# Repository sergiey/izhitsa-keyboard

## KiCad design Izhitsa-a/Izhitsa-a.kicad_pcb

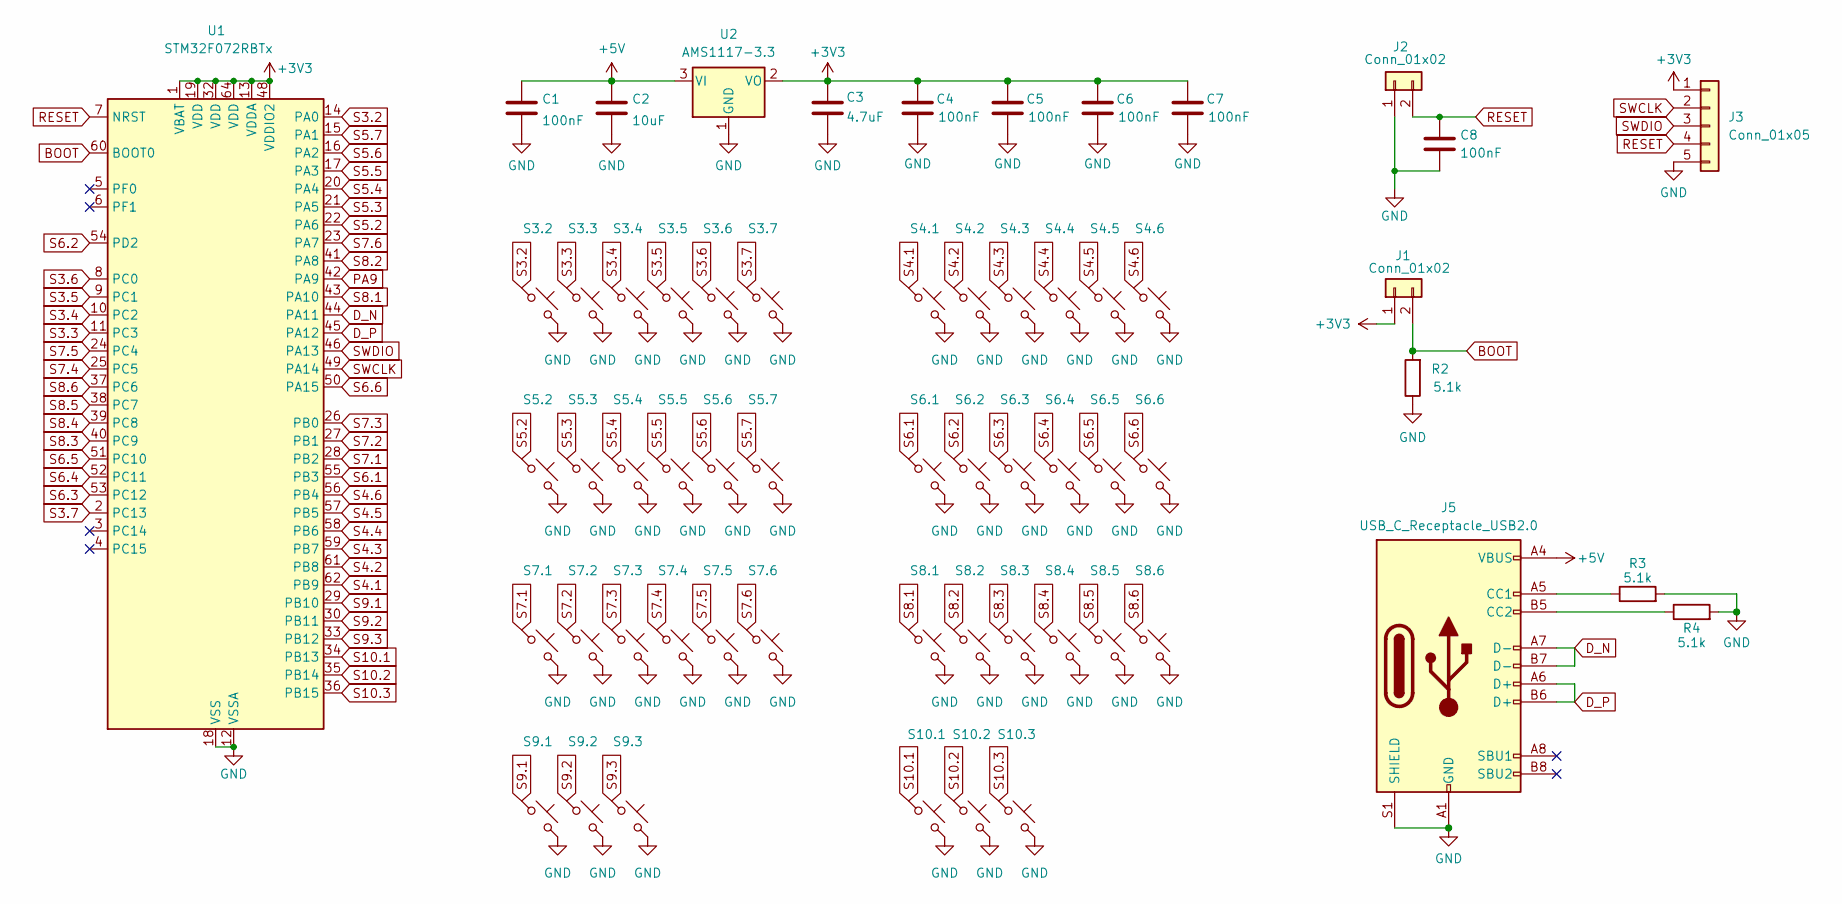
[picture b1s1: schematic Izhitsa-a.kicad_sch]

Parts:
C1, C4, C5, C6, C7, C8: 100nF; C_0603_1608Metric
C2: 10uF; C_0603_1608Metric
C3: 4.7uF; C_0603_1608Metric
J1, J2: Conn_01x02; PinHeader_1x02_P2.54mm_Vertical
J3: Conn_01x05; PinHeader_1x05_P2.54mm_Vertical
J5: USB_C_Receptacle_USB2.0; USB_C_Receptacle_HRO_TYPE-C-31-M-12
R2, R3, R4: 5.1k; R_0603_1608Metric
S3.2, S3.3, S3.4, S3.5, S3.6, S3.7, S4.1, S4.2, S4.3, S4.4, S4.5, S4.6, S5.2, S5.3, S5.4, S5.5, S5.6, S5.7, S6.1, S6.2, S6.3, S6.4, S6.5, S6.6, S7.1, S7.2, S7.3, S7.4, S7.5, S7.6, S8.1, S8.2, S8.3, S8.4, S8.5, S8.6, S9.1, S9.2, S9.3, S10.1, S10.2, S10.3: Keyswitch; Choc_V1_1.00u
U1: STM32F072RBTx; LQFP-64_10x10mm_P0.5mm
U2: AMS1117-3.3; SOT-223-3_TabPin2

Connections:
+3V3: C3.1, C4.1, C5.1, C6.1, C7.1, J1.1, J3.1, U1.1 (VBAT), U1.13 (VDDA), U1.19 (VDD), U1.32 (VDD), U1.48 (VDDIO2), U1.64 (VDD), U2.2 (VO)
+5V: C1.1, C2.1, J5.A4 (VBUS), J5.A9 (VBUS), J5.B4 (VBUS), J5.B9 (VBUS), U2.3 (VI)
BOOT: J1.2, R2.2, U1.60 (BOOT0)
D_N: J5.A7 (D-), J5.B7 (D-), U1.44 (PA11)
D_P: J5.A6 (D+), J5.B6 (D+), U1.45 (PA12)
GND: C1.2, C2.2, C3.2, C4.2, C5.2, C6.2, C7.2, C8.2, J2.1, J3.5, J5.A1 (GND), J5.A12 (GND), J5.B1 (GND), J5.B12 (GND), J5.S1 (SHIELD), R2.1, R3.2, R4.2, S3.2.2, S3.3.2, S3.4.2, S3.5.2, S3.6.2, S3.7.2, S4.1.2, S4.2.2, S4.3.2, S4.4.2, S4.5.2, S4.6.2, S5.2.2, S5.3.2, S5.4.2, S5.5.2, S5.6.2, S5.7.2, S6.1.2, S6.2.2, S6.3.2, S6.4.2, S6.5.2, S6.6.2, S7.1.2, S7.2.2, S7.3.2, S7.4.2, S7.5.2, S7.6.2, S8.1.2, S8.2.2, S8.3.2, S8.4.2, S8.5.2, S8.6.2, S9.1.2, S9.2.2, S9.3.2, S10.1.2, S10.2.2, S10.3.2, U1.12 (VSSA), U1.18 (VSS), U1.31 (VSS), U1.47 (VSS), U1.63 (VSS), U2.1 (GND)
unnamed: J5.A5 (CC1), R3.1
unnamed: J5.B5 (CC2), R4.1
PA9: U1.42 (PA9)
RESET: C8.1, J2.2, J3.4, U1.7 (NRST)
S3.2: S3.2.1, U1.14 (PA0)
S3.3: S3.3.1, U1.11 (PC3)
S3.4: S3.4.1, U1.10 (PC2)
S3.5: S3.5.1, U1.9 (PC1)
S3.6: S3.6.1, U1.8 (PC0)
S3.7: S3.7.1, U1.2 (PC13)
S4.1: S4.1.1, U1.62 (PB9)
S4.2: S4.2.1, U1.61 (PB8)
S4.3: S4.3.1, U1.59 (PB7)
S4.4: S4.4.1, U1.58 (PB6)
S4.5: S4.5.1, U1.57 (PB5)
S4.6: S4.6.1, U1.56 (PB4)
S5.2: S5.2.1, U1.22 (PA6)
S5.3: S5.3.1, U1.21 (PA5)
S5.4: S5.4.1, U1.20 (PA4)
S5.5: S5.5.1, U1.17 (PA3)
S5.6: S5.6.1, U1.16 (PA2)
S5.7: S5.7.1, U1.15 (PA1)
S6.1: S6.1.1, U1.55 (PB3)
S6.2: S6.2.1, U1.54 (PD2)
S6.3: S6.3.1, U1.53 (PC12)
S6.4: S6.4.1, U1.52 (PC11)
S6.5: S6.5.1, U1.51 (PC10)
S6.6: S6.6.1, U1.50 (PA15)
S7.1: S7.1.1, U1.28 (PB2)
S7.2: S7.2.1, U1.27 (PB1)
S7.3: S7.3.1, U1.26 (PB0)
S7.4: S7.4.1, U1.25 (PC5)
S7.5: S7.5.1, U1.24 (PC4)
S7.6: S7.6.1, U1.23 (PA7)
S8.1: S8.1.1, U1.43 (PA10)
S8.2: S8.2.1, U1.41 (PA8)
S8.3: S8.3.1, U1.40 (PC9)
S8.4: S8.4.1, U1.39 (PC8)
S8.5: S8.5.1, U1.38 (PC7)
S8.6: S8.6.1, U1.37 (PC6)
S9.1: S9.1.1, U1.29 (PB10)
S9.2: S9.2.1, U1.30 (PB11)
S9.3: S9.3.1, U1.33 (PB12)
S10.1: S10.1.1, U1.34 (PB13)
S10.2: S10.2.1, U1.35 (PB14)
S10.3: S10.3.1, U1.36 (PB15)
SWCLK: J3.2, U1.49 (PA14)
SWDIO: J3.3, U1.46 (PA13)

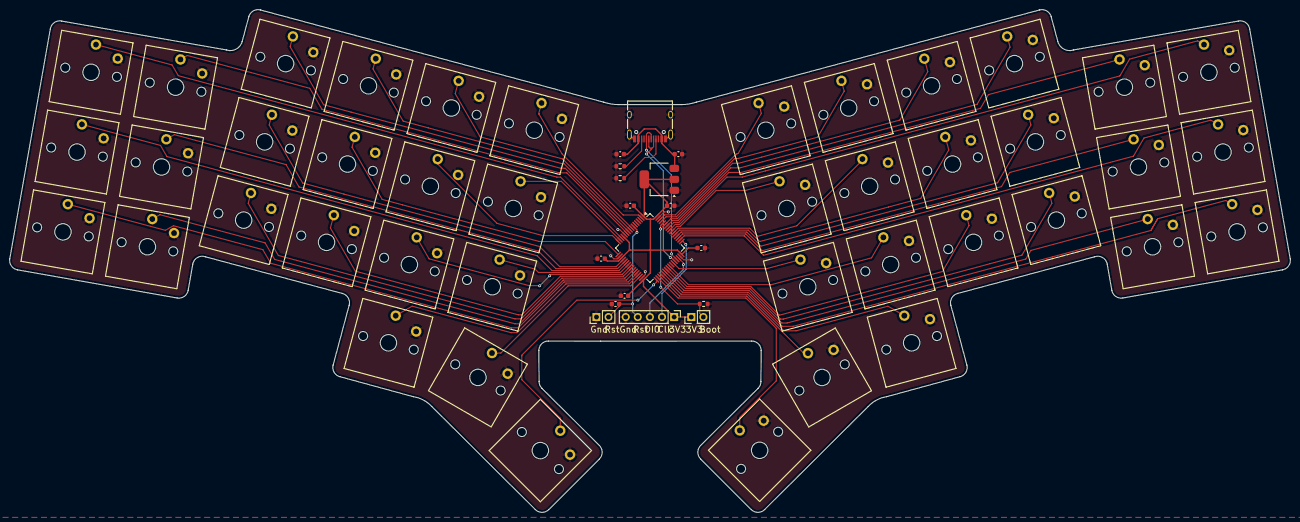
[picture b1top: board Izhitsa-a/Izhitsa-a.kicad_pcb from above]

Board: 2 copper layers, 268.7 x 105.5 mm, 59 parts (0 on the bottom side), 53 nets.

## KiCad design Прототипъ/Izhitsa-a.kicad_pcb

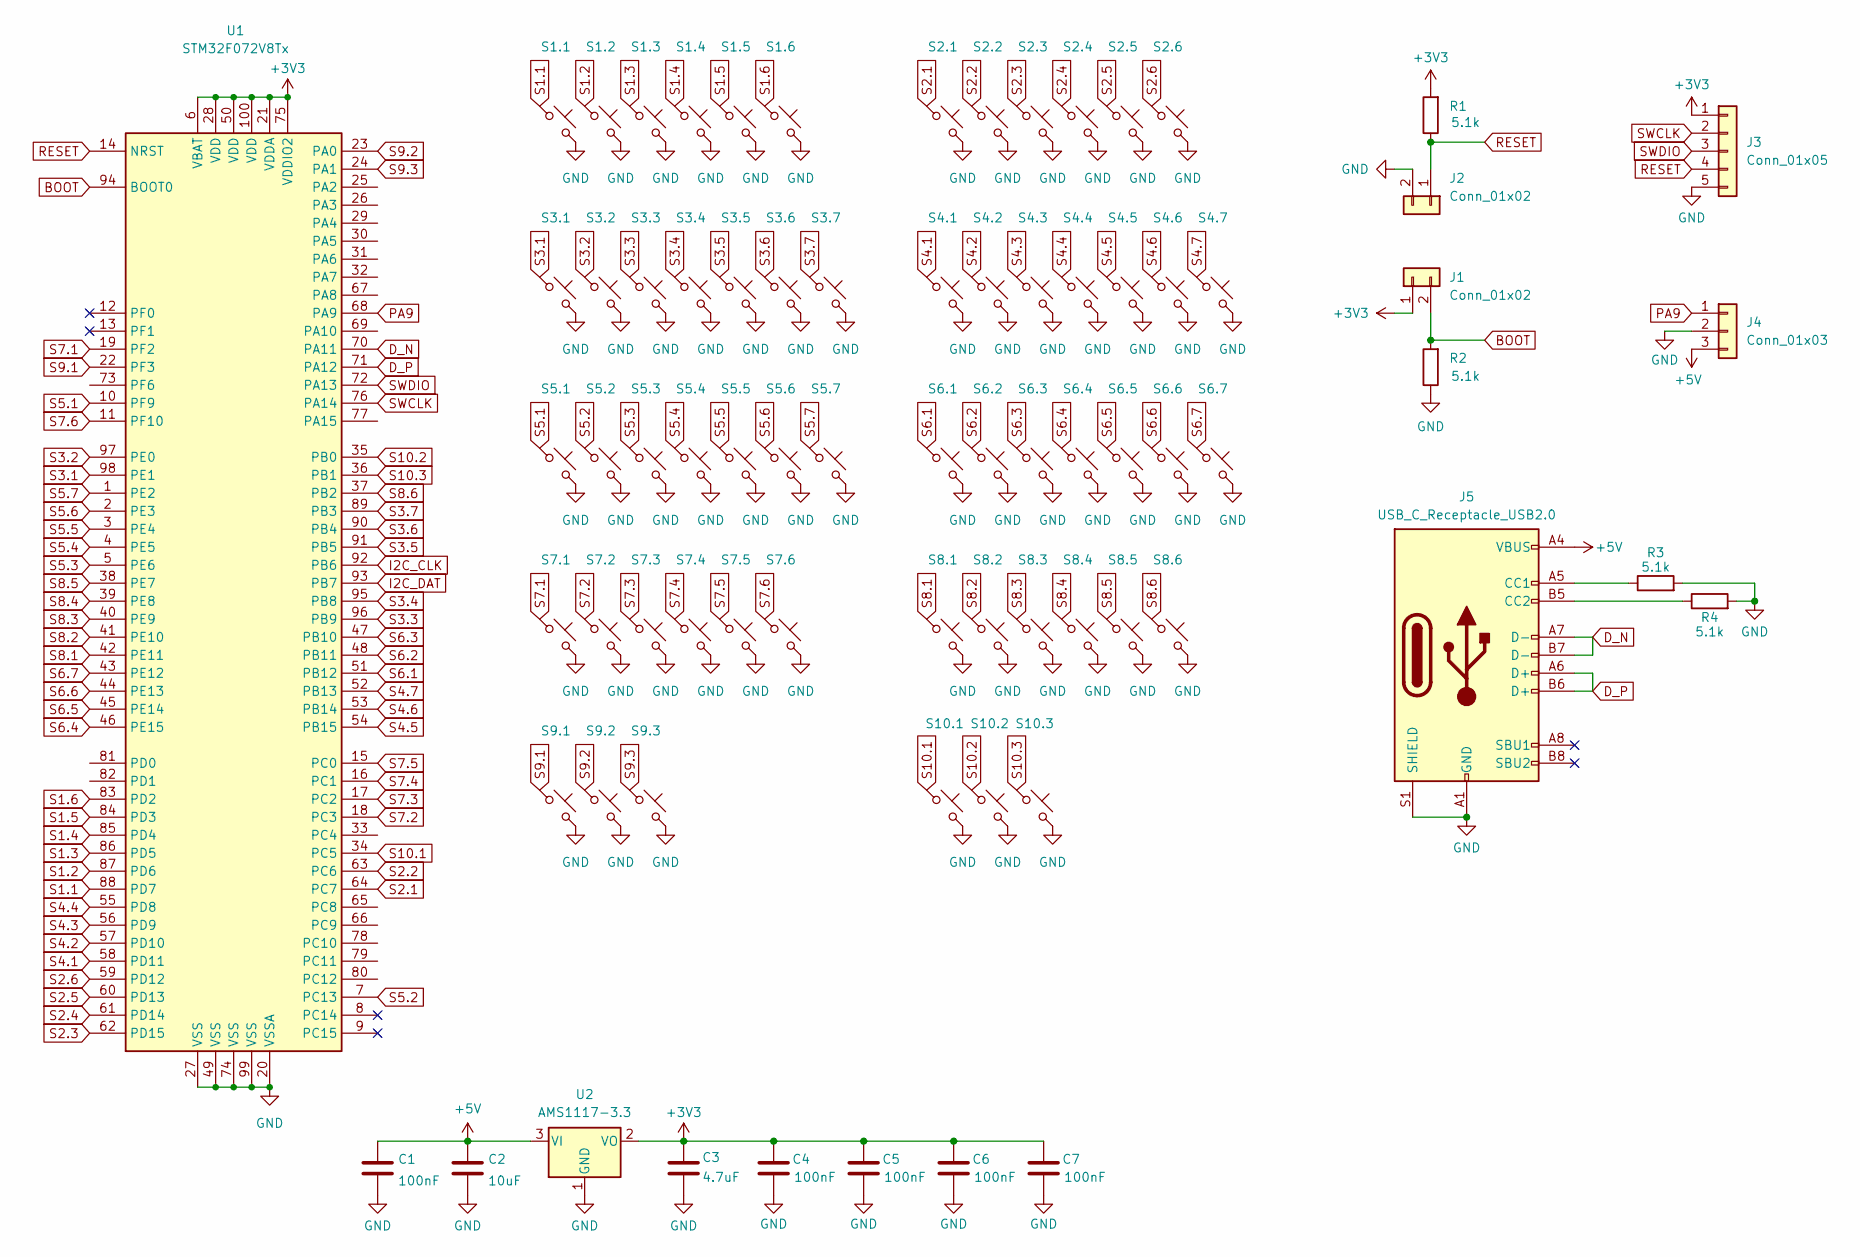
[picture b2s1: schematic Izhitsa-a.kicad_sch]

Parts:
C1, C4, C5, C6, C7: 100nF; C_0603_1608Metric
C2: 10uF; C_0603_1608Metric
C3: 4.7uF; C_0603_1608Metric
J1, J2: Conn_01x02; PinHeader_1x02_P2.54mm_Vertical
J3: Conn_01x05; PinHeader_1x05_P2.54mm_Vertical
J4: Conn_01x03; PinHeader_1x03_P2.54mm_Vertical
J5: USB_C_Receptacle_USB2.0; USB_C_Receptacle_HRO_TYPE-C-31-M-12
R1, R2, R3, R4: 5.1k; R_0603_1608Metric
S1.1, S1.2, S1.3, S1.4, S1.5, S1.6, S2.1, S2.2, S2.3, S2.4, S2.5, S2.6, S3.1, S3.2, S3.3, S3.4, S3.5, S3.6, S3.7, S4.1, S4.2, S4.3, S4.4, S4.5, S4.6, S4.7, S5.1, S5.2, S5.3, S5.4, S5.5, S5.6, S5.7, S6.1, S6.2, S6.3, S6.4, S6.5, S6.6, S6.7, S7.1, S7.2, S7.3, S7.4, S7.5, S7.6, S8.1, S8.2, S8.3, S8.4, S8.5, S8.6, S9.1, S9.2, S9.3, S10.1, S10.2, S10.3: Keyswitch; Choc_V1_1.00u
U1: STM32F072V8Tx; LQFP-100_14x14mm_P0.5mm
U2: AMS1117-3.3; SOT-223-3_TabPin2

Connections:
+3V3: C3.1, C4.1, C5.1, C6.1, C7.1, J1.1, J3.1, R1.2, U1.6 (VBAT), U1.21 (VDDA), U1.28 (VDD), U1.50 (VDD), U1.75 (VDDIO2), U1.100 (VDD), U2.2 (VO)
+5V: C1.1, C2.1, J4.3, J5.A4 (VBUS), J5.A9 (VBUS), J5.B4 (VBUS), J5.B9 (VBUS), U2.3 (VI)
BOOT: J1.2, R2.2, U1.94 (BOOT0)
D_N: J5.A7 (D-), J5.B7 (D-), U1.70 (PA11)
D_P: J5.A6 (D+), J5.B6 (D+), U1.71 (PA12)
GND: C1.2, C2.2, C3.2, C4.2, C5.2, C6.2, C7.2, J2.2, J3.5, J4.2, J5.A1 (GND), J5.A12 (GND), J5.B1 (GND), J5.B12 (GND), J5.S1 (SHIELD), R2.1, R3.2, R4.2, S1.1.2, S1.2.2, S1.3.2, S1.4.2, S1.5.2, S1.6.2, S2.1.2, S2.2.2, S2.3.2, S2.4.2, S2.5.2, S2.6.2, S3.1.2, S3.2.2, S3.3.2, S3.4.2, S3.5.2, S3.6.2, S3.7.2, S4.1.2, S4.2.2, S4.3.2, S4.4.2, S4.5.2, S4.6.2, S4.7.2, S5.1.2, S5.2.2, S5.3.2, S5.4.2, S5.5.2, S5.6.2, S5.7.2, S6.1.2, S6.2.2, S6.3.2, S6.4.2, S6.5.2, S6.6.2, S6.7.2, S7.1.2, S7.2.2, S7.3.2, S7.4.2, S7.5.2, S7.6.2, S8.1.2, S8.2.2, S8.3.2, S8.4.2, S8.5.2, S8.6.2, S9.1.2, S9.2.2, S9.3.2, S10.1.2, S10.2.2, S10.3.2, U1.20 (VSSA), U1.27 (VSS), U1.49 (VSS), U1.74 (VSS), U1.99 (VSS), U2.1 (GND)
I2C_CLK: U1.92 (PB6)
I2C_DAT: U1.93 (PB7)
unnamed: J5.A5 (CC1), R3.1
unnamed: J5.B5 (CC2), R4.1
PA9: J4.1, U1.68 (PA9)
RESET: J2.1, J3.4, R1.1, U1.14 (NRST)
S1.1: S1.1.1, U1.88 (PD7)
S1.2: S1.2.1, U1.87 (PD6)
S1.3: S1.3.1, U1.86 (PD5)
S1.4: S1.4.1, U1.85 (PD4)
S1.5: S1.5.1, U1.84 (PD3)
S1.6: S1.6.1, U1.83 (PD2)
S2.1: S2.1.1, U1.64 (PC7)
S2.2: S2.2.1, U1.63 (PC6)
S2.3: S2.3.1, U1.62 (PD15)
S2.4: S2.4.1, U1.61 (PD14)
S2.5: S2.5.1, U1.60 (PD13)
S2.6: S2.6.1, U1.59 (PD12)
S3.1: S3.1.1, U1.98 (PE1)
S3.2: S3.2.1, U1.97 (PE0)
S3.3: S3.3.1, U1.96 (PB9)
S3.4: S3.4.1, U1.95 (PB8)
S3.5: S3.5.1, U1.91 (PB5)
S3.6: S3.6.1, U1.90 (PB4)
S3.7: S3.7.1, U1.89 (PB3)
S4.1: S4.1.1, U1.58 (PD11)
S4.2: S4.2.1, U1.57 (PD10)
S4.3: S4.3.1, U1.56 (PD9)
S4.4: S4.4.1, U1.55 (PD8)
S4.5: S4.5.1, U1.54 (PB15)
S4.6: S4.6.1, U1.53 (PB14)
S4.7: S4.7.1, U1.52 (PB13)
S5.1: S5.1.1, U1.10 (PF9)
S5.2: S5.2.1, U1.7 (PC13)
S5.3: S5.3.1, U1.5 (PE6)
S5.4: S5.4.1, U1.4 (PE5)
S5.5: S5.5.1, U1.3 (PE4)
S5.6: S5.6.1, U1.2 (PE3)
S5.7: S5.7.1, U1.1 (PE2)
S6.1: S6.1.1, U1.51 (PB12)
S6.2: S6.2.1, U1.48 (PB11)
S6.3: S6.3.1, U1.47 (PB10)
S6.4: S6.4.1, U1.46 (PE15)
S6.5: S6.5.1, U1.45 (PE14)
S6.6: S6.6.1, U1.44 (PE13)
S6.7: S6.7.1, U1.43 (PE12)
S7.1: S7.1.1, U1.19 (PF2)
S7.2: S7.2.1, U1.18 (PC3)
S7.3: S7.3.1, U1.17 (PC2)
S7.4: S7.4.1, U1.16 (PC1)
S7.5: S7.5.1, U1.15 (PC0)
S7.6: S7.6.1, U1.11 (PF10)
S8.1: S8.1.1, U1.42 (PE11)
S8.2: S8.2.1, U1.41 (PE10)
S8.3: S8.3.1, U1.40 (PE9)
S8.4: S8.4.1, U1.39 (PE8)
S8.5: S8.5.1, U1.38 (PE7)
S8.6: S8.6.1, U1.37 (PB2)
S9.1: S9.1.1, U1.22 (PF3)
S9.2: S9.2.1, U1.23 (PA0)
S9.3: S9.3.1, U1.24 (PA1)
S10.1: S10.1.1, U1.34 (PC5)
S10.2: S10.2.1, U1.35 (PB0)
S10.3: S10.3.1, U1.36 (PB1)
SWCLK: J3.2, U1.76 (PA14)
SWDIO: J3.3, U1.72 (PA13)

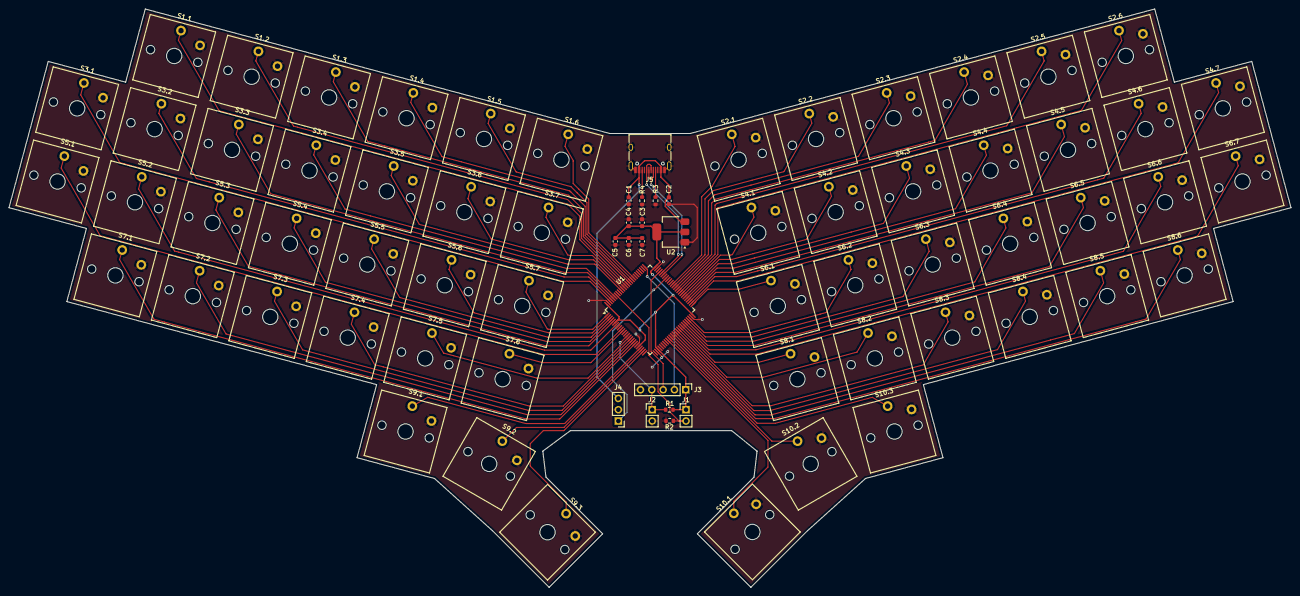
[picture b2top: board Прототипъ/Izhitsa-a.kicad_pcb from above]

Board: 2 copper layers, 287.8 x 129.8 mm, 76 parts (0 on the bottom side), 70 nets.

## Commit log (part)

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2024-06-01 Update gitignore
2024-06-01 Add Izhitsa A and prototype
2024-06-01 Add signature.png
2024-08-31 Add QMK keyboard layout
2024-09-05 Add xcompose
2024-09-09 Fix xcompose
2024-09-09 Update keymap
2024-09-19 Add gerber files
2024-09-22 Update layout
2025-04-02 Add firmware ver. 1
2025-04-08 Add new firmware
2025-04-13 Add firmware ver. 1.2
2025-04-16 Add firmware ver. 1.3
2025-05-21 Add firmware ver. 1.4
